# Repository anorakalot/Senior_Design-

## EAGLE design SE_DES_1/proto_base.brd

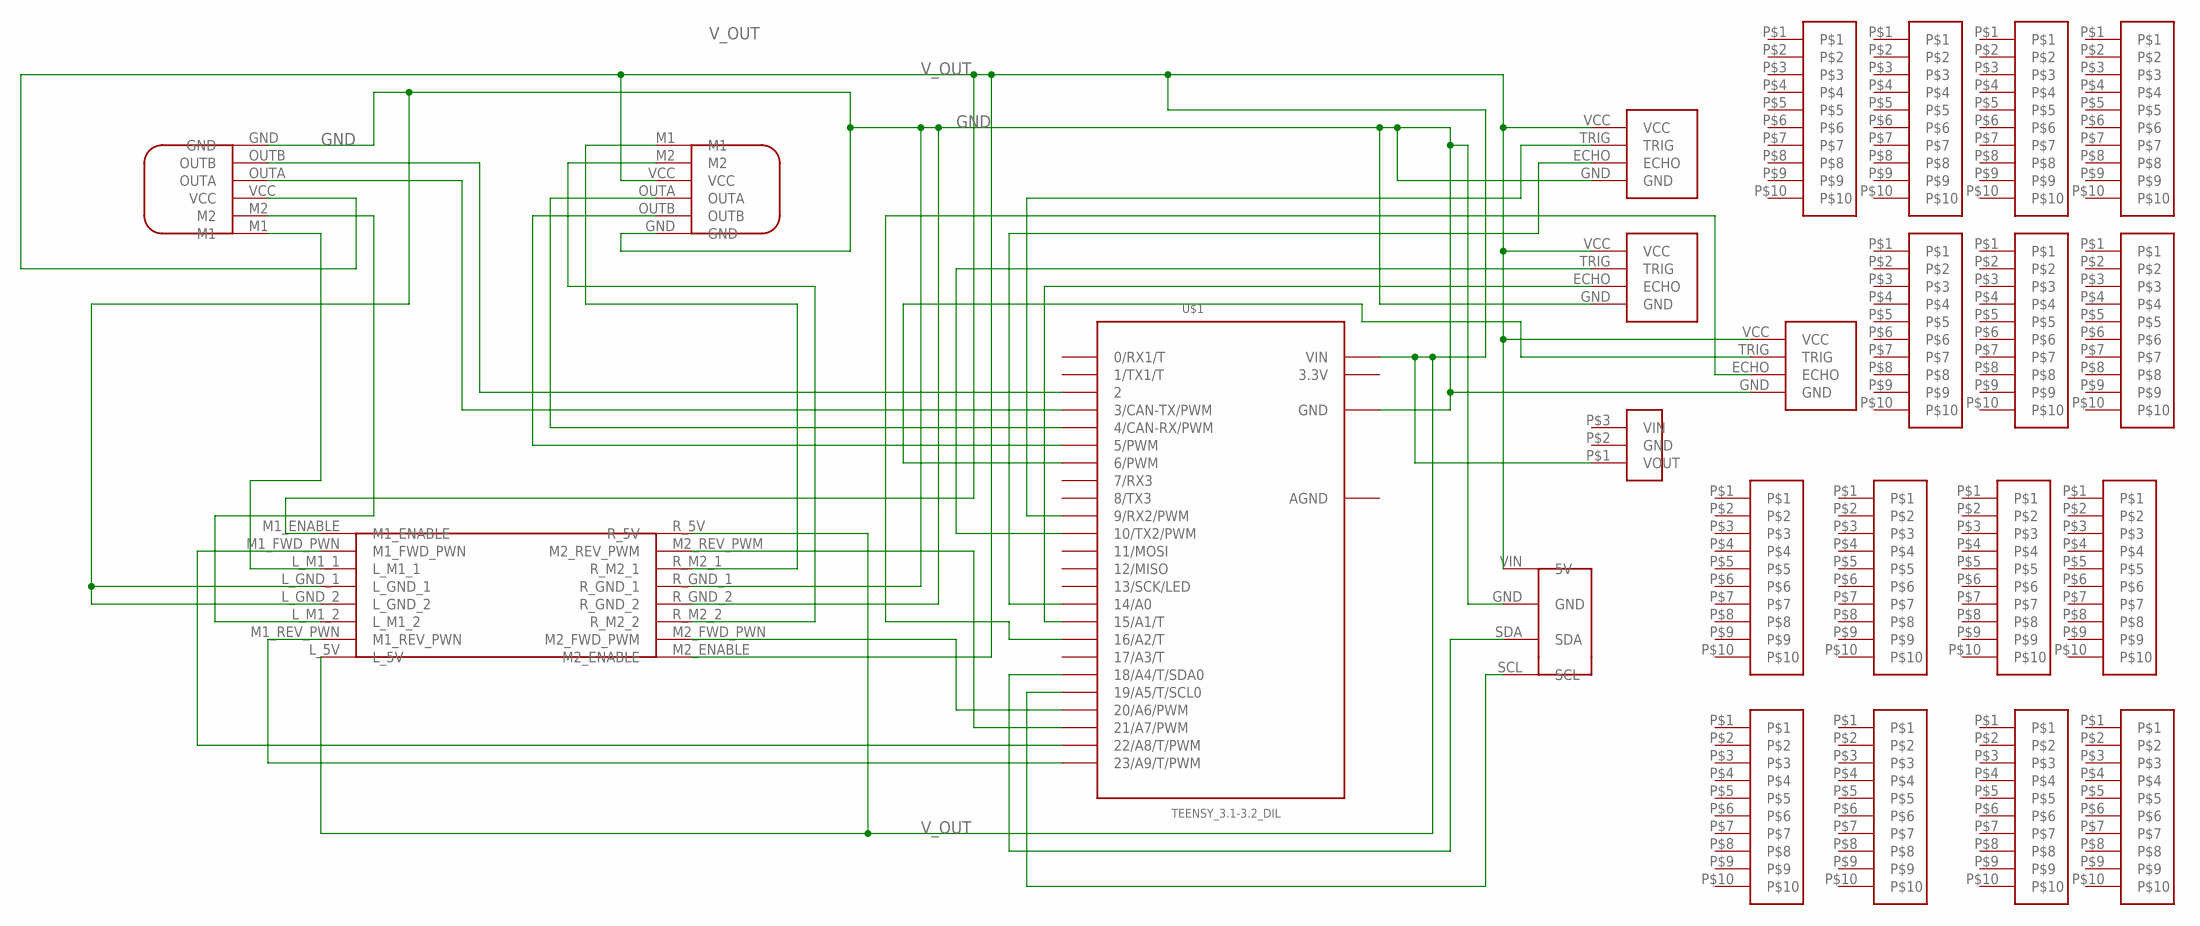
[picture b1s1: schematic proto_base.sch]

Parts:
IMU: IMU
LEFT_ENCODER: MOTOR_ENCODER
MOTOR_DRIVER: MOTOR_DRIVER
RIGHT_ENCODER: MOTOR_ENCODER
U$1: TEENSY_3.1-3.2_DIL; TEENSY_3.0-3.2&LC_DIL
U$2: VOLTAGE_REGULATOR
U$3, U$4, U$5: SONAR_SENSOR
U$6, U$7, U$8, U$9, U$10, U$11, U$12, U$13, U$14, U$15, U$16, U$17, U$18, U$19, U$20: TEST_ROW

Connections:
3.3V: U$1.3.3V
AGND: U$1.AGND
GND: IMU.GND, LEFT_ENCODER.GND, MOTOR_DRIVER.L_GND_1, MOTOR_DRIVER.L_GND_2, MOTOR_DRIVER.R_GND_1, MOTOR_DRIVER.R_GND_2, RIGHT_ENCODER.GND, U$1.GND, U$3.GND, U$4.GND, U$5.GND
unnamed: LEFT_ENCODER.OUTB, U$1.2
unnamed: LEFT_ENCODER.OUTA, U$1.3 (3/CAN-TX/PWM)
unnamed: RIGHT_ENCODER.OUTA, U$1.4 (4/CAN-RX/PWM)
unnamed: RIGHT_ENCODER.OUTB, U$1.5 (5/PWM)
unnamed: LEFT_ENCODER.M2, MOTOR_DRIVER.L_M1_2
unnamed: LEFT_ENCODER.M1, MOTOR_DRIVER.L_M1_1
unnamed: U$1.9 (9/RX2/PWM), U$3.TRIG
unnamed: U$1.14/A0, U$3.ECHO
unnamed: IMU.SDA, U$1.18/A4 (18/A4/T/SDA0)
unnamed: MOTOR_DRIVER.M1_REV_PWN, U$1.23/A9 (23/A9/T/PWM)
unnamed: MOTOR_DRIVER.M1_FWD_PWN, U$1.22/A8 (22/A8/T/PWM)
unnamed: MOTOR_DRIVER.M2_REV_PWM, U$1.21/A7 (21/A7/PWM)
unnamed: MOTOR_DRIVER.M2_FWD_PWN (M2_FWD_PWM), U$1.20/A6 (20/A6/PWM)
unnamed: MOTOR_DRIVER.R_M2_1, RIGHT_ENCODER.M1
unnamed: MOTOR_DRIVER.R_M2_2, RIGHT_ENCODER.M2
unnamed: IMU.SCL, U$1.19/A5 (19/A5/T/SCL0)
unnamed: U$1.10 (10/TX2/PWM), U$4.TRIG
unnamed: U$1.15/A1 (15/A1/T), U$4.ECHO
unnamed: U$1.6 (6/PWM), U$5.TRIG
unnamed: U$1.16/A2 (16/A2/T), U$5.ECHO
V_OUT: IMU.VIN (5V), LEFT_ENCODER.VCC, MOTOR_DRIVER.L_5V, MOTOR_DRIVER.M1_ENABLE, MOTOR_DRIVER.M2_ENABLE, MOTOR_DRIVER.R_5V, RIGHT_ENCODER.VCC, U$1.VIN, U$2.P$1 (VOUT), U$3.VCC, U$4.VCC, U$5.VCC

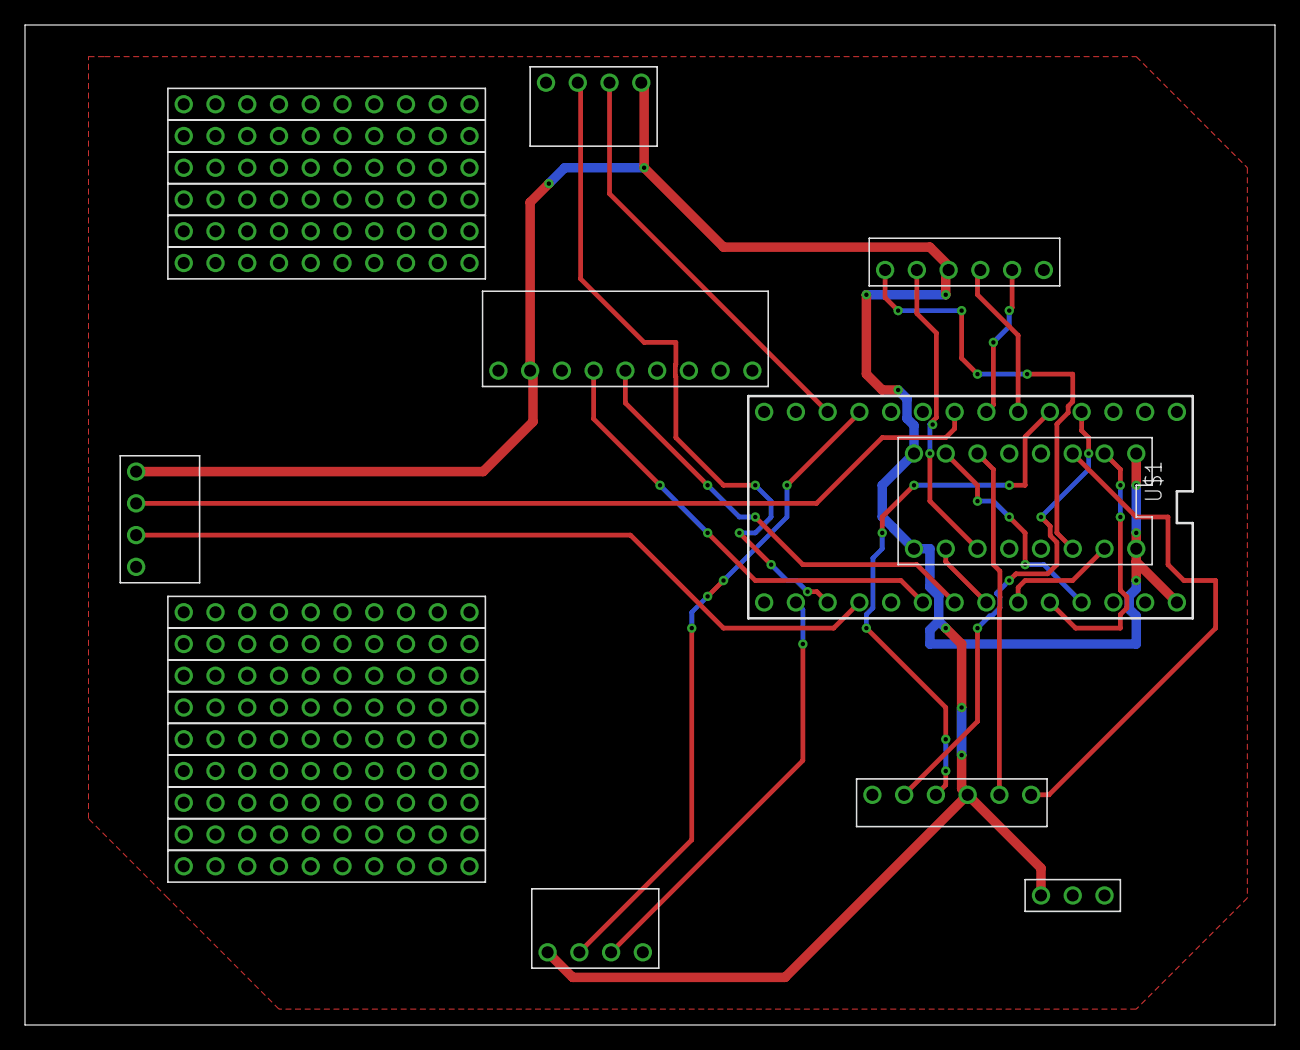
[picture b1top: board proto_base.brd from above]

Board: 2 copper layers, 100.0 x 80.0 mm, 24 parts (0 on the bottom side), 22 nets.

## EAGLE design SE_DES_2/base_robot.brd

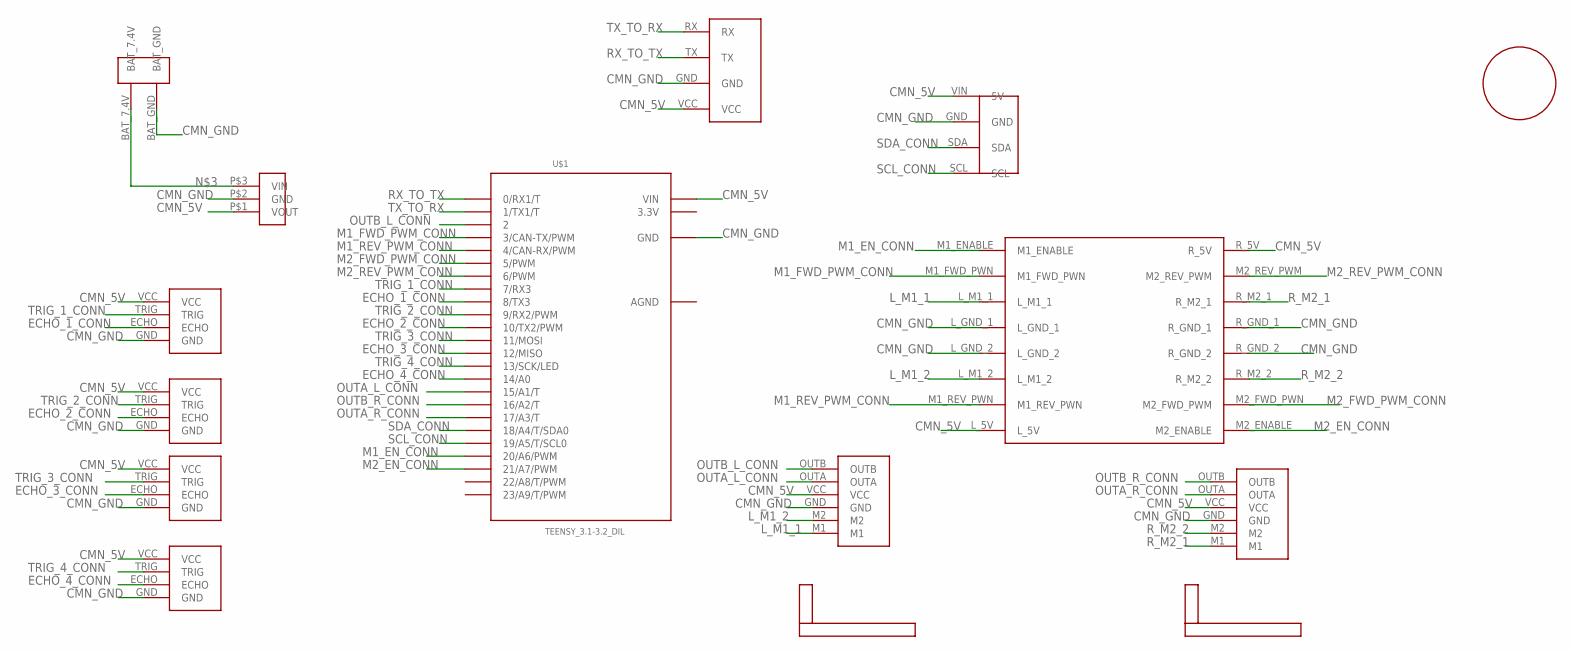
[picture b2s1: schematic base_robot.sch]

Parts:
U$1: TEENSY_3.1-3.2_DIL; TEENSY_3.0-3.2&LC_DIL
U$2: MOTOR_DRIVER
U$3: VOLTAGE_REGULATOR
U$4, U$5, U$6, U$7: SONAR_SENSOR
U$8: BATTERY_INPUT
U$9, U$10: MOTOR_ENCODER_25D
U$11: IMU
U$12: HC05_BLUETOOTH
U$13: 3_4_BALLCASTER
U$14, U$15: MOTOR_BRACKET_25D

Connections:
3.3V: U$1.3.3V
AGND: U$1.AGND
CMN_5V: U$1.VIN, U$2.L_5V, U$2.R_5V, U$3.P$1 (VOUT), U$4.VCC, U$5.VCC, U$6.VCC, U$7.VCC, U$9.VCC, U$10.VCC, U$11.VIN (5V), U$12.VCC
CMN_GND: U$1.GND, U$2.L_GND_1, U$2.L_GND_2, U$2.R_GND_1, U$2.R_GND_2, U$3.P$2 (GND), U$4.GND, U$5.GND, U$6.GND, U$7.GND, U$8.BAT_GND, U$9.GND, U$10.GND, U$11.GND, U$12.GND
ECHO_1_CONN: U$1.8 (8/TX3), U$4.ECHO
ECHO_2_CONN: U$1.10 (10/TX2/PWM), U$5.ECHO
ECHO_3_CONN: U$1.12 (12/MISO), U$6.ECHO
ECHO_4_CONN: U$1.14/A0, U$7.ECHO
L_M1_1: U$2.L_M1_1, U$9.M1
L_M1_2: U$2.L_M1_2, U$9.M2
M1_EN_CONN: U$1.20/A6 (20/A6/PWM), U$2.M1_ENABLE
M1_FWD_PWM_CONN: U$1.3 (3/CAN-TX/PWM), U$2.M1_FWD_PWN
M1_REV_PWM_CONN: U$1.4 (4/CAN-RX/PWM), U$2.M1_REV_PWN
M2_EN_CONN: U$1.21/A7 (21/A7/PWM), U$2.M2_ENABLE
M2_FWD_PWM_CONN: U$1.5 (5/PWM), U$2.M2_FWD_PWN (M2_FWD_PWM)
M2_REV_PWM_CONN: U$1.6 (6/PWM), U$2.M2_REV_PWM
unnamed: U$3.P$3 (VIN), U$8.BAT_7.4V
OUTA_L_CONN: U$1.15/A1 (15/A1/T), U$9.OUTA
OUTA_R_CONN: U$1.17/A3 (17/A3/T), U$10.OUTA
OUTB_L_CONN: U$1.2, U$9.OUTB
OUTB_R_CONN: U$1.16/A2 (16/A2/T), U$10.OUTB
RX_TO_TX: U$1.0 (0/RX1/T), U$12.TX
R_M2_1: U$2.R_M2_1, U$10.M1
R_M2_2: U$2.R_M2_2, U$10.M2
SCL_CONN: U$1.19/A5 (19/A5/T/SCL0), U$11.SCL
SDA_CONN: U$1.18/A4 (18/A4/T/SDA0), U$11.SDA
TRIG_1_CONN: U$1.7 (7/RX3), U$4.TRIG
TRIG_2_CONN: U$1.9 (9/RX2/PWM), U$5.TRIG
TRIG_3_CONN: U$1.11 (11/MOSI), U$6.TRIG
TRIG_4_CONN: U$1.13 (13/SCK/LED), U$7.TRIG
TX_TO_RX: U$1.1 (1/TX1/T), U$12.RX

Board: 2 copper layers, 15 parts (0 on the bottom side), 29 nets, no tracks yet.

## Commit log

2021-11-02 Create LICENSE
2021-11-02 senior design proto code arduino
2021-12-25 Second Version of PCB of base mapping robot
2021-12-25 PCB Libraries I made for Senior Design PCB Base Robot
2021-12-25 test code for the motor and sonar systems respectively
2021-12-25 made new motor bracket 25D library for bigger 25D motors
2021-12-25 pcb files for sen des se_des_2 is the latest one
2022-02-12 imu works! now need to do testing to get rid of drift
2022-02-22 have controller setpoint go straight
2022-02-22 setpoint values 0.70 goes pretty straight
2022-02-24 added commenst for end of brackets
2022-02-24 fixed go one cell function
2022-02-25 micro_adj_code is done
2022-02-26 updated sonar for left and middle sensors
    need to test again when right sensor is reattached
2022-02-26 integrated sonar into it, also made it not start unless sonar
2022-02-26 communication working
2022-02-26 works communication with test 4 (which was test 2)
2022-02-27 did teensy communication function
2022-02-27 got cells to get starting cost right
2022-02-28 version that works but not at correct x y values but still gets to center.
2022-02-28 does get to end cell need to test for obstacles
2022-02-28 tremaux is DONE! Gives right direction val, fixed all to y x coord types
2022-02-28 before integrating tremaux search function
2022-02-28 issues w/ forward_w_enc and reverse_w_enc going back and forth
2022-02-28 before changing motor func to fix forw reverse in sonar adj
2022-02-28 go_one_cell goes straight
2022-02-28 adjust_sonar func works , gonna take out comments in next upload
2022-02-28 state machine is done prototype version of it at least
2022-02-28 does state machine traversal need to do offset and get rid of extra go one cell at the end
2022-02-28 fixed extra go_one_cell
2022-02-28 setpoints make it go straight after it gets to the correct values, gonna do more changes
2022-02-28 goes straight veers left oveer time 0.66 0.64
2022-02-28 goes REALLY STRAIGHT CHANGED KD TO CHANGE TO DESIRED PWM FASTER
2022-02-28 right before testing_micro adj had to move func tgo motor.h to compile
2022-02-28 gonna get rid of all serial prints and already should've gotten rid of delay also going to delete comments of old unused code
2022-02-28 micro_adj is mostly done, going to put halt_sec in enc/turn functions
2022-03-01 demo_submit_gonna_take_out serial
2022-03-01 tech demo submit
2022-03-04 made changes to micro_adj to stop weird stops,VIDEO DEMO CODE
2022-03-04 smoother micro adjustments (did video demo)
2022-03-04 fixed issue with tremaux not going into final goal cell
2022-03-04 fixed sonar bug in tremaux, now need to fix tremaux prior going up/right
2022-03-04 does use sonar to find obstacles correctly now using up prior going up and right first
2022-03-05 added back in sonar check right, before adding in new state to look for cup
2022-03-05 added if statement in state machine to go back to Adjust State if sonar not at correct range
2022-03-06 added find cup function that does 20 left turn enc turns , BEFORE TWEAKING kp FOR STRAIGHTNESS IN NEW BUILD
2022-03-07 demo video code used
